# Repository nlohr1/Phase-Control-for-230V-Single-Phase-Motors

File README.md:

### Readme-Content:
- [Basic Schematic](#phase-control-for-230v-single-phase-motors-v2)
- [Module-Alignments](#alignment-v2-of-used-modules-on-a-5mm-acrylic-base-board)
- [Main-Schematic](#main-schematic--wiring-connections)
- [Safety-features](#safety-features)
- [Disclaimer](#readme-contents)
- [Principle-description](#principle-description)
- [The Wiring Board](#the-wiring-board)
- [Speedometer](#speedometer)
- [Schematic and Layout of the DIY-Speedometer](#diy-speedometer)
- [DIY-Boards + PCB-Layout](#diy-boards)

# Phase-Control-for-230V-Single-Phase-Motors
### Corrections and small modifications on new version Main_v2:  
- Another alignment purpose, which saves space.  
- The Emergency-Switch now is placed correctly within the "Off"-Switch wiring-line. Previoulsy it was wrongly placed within "On"-Switch line.  
- A second, passive 220k&Omega;2W-Resistor is placed after the Reversing-Switch between the two Motor-Supply-Lines (U1 and U2), instead on the wiring-board, to ensure save voltage-unload of the Motor-"Fire" EMI-Filter.

**⇒ &nbsp;New files in v2:**  
&#45; Main_v2 (base-folder for v2)  
&#45; Wiring-Board-Nano_v2 (sub-folder)  

This is a Control-Board for direction-switchable 230V *direct current* (DC)-motors, whose speed (rpm) can be controlled using a Potentiometer *or*  
using a PWM (Pulse Width Modulation) Signal in the low voltage range, generated here by a microController (Arduino Nano).

&nbsp; &nbsp;*Phase-Control schematic: **Priciple for 230V DC-Motors** with reversing-switch.*  

The picture above shows a basic diagram for the electronic control of a 230V **DC** motor, e.g. a hobby lathe, connected to a **single-phase** (230V) **AC**-current network.

Phase control circuits are often used for simple speed controls, here with an additional Bridge-Rectifier for 230V DC electric motors,
which are often used in medium power hobby machines (up to 10 amps ≙ approx. 2300 watts), such as lathes, milling benches, etc.

### Alignment-v2 of used modules on a 5mm acrylic base-board:
  
Since electronic controls of 230V *DC* motors in today's hobby machines (such as lathes, milling benches, etc.) often are built with
inexpensive components that are not really protected against surges or current peaks – some electronic-failures are inevitable.
So I decided to use a circuit that works a little more reliable, with electronic components and *modules* that are readily available
on the market *and* at the same time are better protected against voltage-glitches, overloads, incorrect operations and engine over-temperature.
All 230VDC (Direct Current!) brushed motors with up-to 2300 Watts can be controlled with this phase control board. It allows to control
the speed of the motor (0-100%) as well as the motor direction of rotation.

### Main Schematic / Wiring Connections:
⇒ *(the DIY-Wiring-Board with the Ardujino-nano here is yellow-framed)*

## Safety features
This circuit has some essential safety-functions:
- The main module "Kemo-M240" used here contains an integrated soft start, needed to start up strong motors (>800 - 2300 Watts),
   to avoid the tripping of standard 16A household fuses
- This main-module also contains an automatic overload or anti-lock shutdown with electronic reset
- If the used Motor contains a built-in NTC-thermistor (with 100kOhm), the µController can provide a protection against
   engine overheatings: if the motor-temperature exceeds 80°C, the µC goes into an endless loop, and reactivating PWM
   is only possible by switching off (main-power) or by pushing the reset-button of the µC.

!!!: Protection against direction of rotation switching ***while driving*** is **NOT** provided: if so an "EMF short circuit" occurs,
the "Kemo-M240" controller shots the power-control off in a fractions of a second and thus at least the mechanics of the machine is protected.
Electronics then can only be reactivated after a complete restart - either per µContoller-Reset or after a complete Main-Power Shutdown.

## Disclaimer:  
!!! It goes without saying that you reproduce this circuit at your own risk and responsibility !!!
Anyone who does not have sufficient knowledge of how to handle *dangerous* 230VAC currents or 325VDC(ss) voltages(!):
If you are not familiar with electrical or electronic components, you should either hire a specialist to do it for you
or stay away from it!
“Experiments” without special knowledge and appropriate protection(s) on high voltages can quickly end in death
following an electric shock! And sudden cardiac-arrest can occur even days after an electric shock! - if then
no immediate help is nearby...
In any case, a replica of this project is done expressly and explicitly *at your own risk*!

**Further notes:**
- Three-phase motor control is excluded due to the principle! This circuit only controls single phase Engines!
- The circuit also works with (simpler) *AC* single-phase asynchronous motors - omitting the bridge rectifier used here.
   However, a connected ***AC*** motor then is no longer direction-reversible.
- It is NOT suitable for capacitor motors! - "Capacitor starting motors" are often only used for simple purposes and
   built+used for on/off operation only (such as for smaller hobby drill press machines) - and are not speed-regulated.
   But it depends specifically on the type of engine, some capacitor motors can still be regulated (speed-limited).
   However, any weak to poor efficiency that so occurs should be taken into account (including heat losses).

Factual suggestions for improvements and changes are always welcome!

## Principle description:
The control works according to the 230VAC phase control principle (similar to a lamp dimmer), but in contrast to this
it can neutralize EMF (electromotive forces) of greater motors and is determined by special selection of used electronic components.

The Kemo-240 control-module is controlled via PWM (Pulse Width Modulation). This (low-voltage: 5VDC) PWM-signal is generated
with a “Arduino-Nano” micro-controller and (if present), this µC also evaluates an NTC-Sensor installed within the Motor, to check
a possible motor-overtemperature.
The Speedometer (RPM display on a LED display) does not run - as usually *independently* of the main phase-control, 
but sends back a "busy" signal to the µController, which therefore "knows" when the motor is running or not
(=when it is standing still), in order to ensure active discharge of the triac snubber and the EMI or EMC-filters charged
through supplied voltages + motor back EMF, to avoid uncontrolled jerky startings of the DC-motor after changing the direction of rotation.

The control consists of several modules chained(wired) one behind the other:

1. the 10AT fuse (F1) and the on/off switch with the self-holding latching contactor,
2. the (mandatory) safety switches plus other 230V safety microswitches on the specific machine,
3. the upstream EMC filter (= ElectroMagnetic Compatibility), here called EMI filter (serves to avoid incoming E.M. interferences),
4. the actual (triac) phase control, using *either* a potentiometer *or* a µController with PWM-output (Pulse-Width Modulation),
5. in parallel the 5V low-voltage circuit with the "Arduino-Nano" module, to generate the PWM for the phase control (2nd. version), 
   with additional, software-side monitoring of eventual motor-over-temperature,
6. the 15A/1500V bridge rectifier,
7. the reversing switch, also called “pole inverter” or direction of rotation switch,
8. a second EMI (carbon-brush-"fire"-) suppression filter + a second 10AT motor fuse (F2), and
9. at last the 325V DC (=direct current) motor.

230v-Wiring between modules and the outside-parts (rear 230V inlet-panel, front machine-control-panel, motor-connections) have to be connected safely
through PVC-isolated 1mm² wires (about AWG 17) and in-between through isolated threaded-connectors or clamping-connectors with 16A/230V.
I used lever clamps ("WAGO Hebelklemme 221-2411") for most of the "flying"-connections.  
For all 5Volt (=low-voltage) connections I used smaller wires (about 0.25-0.75mm² = AWG-23 upto AWG-20) with JST-Connectors (2-, 3- and 4-wired),
as connectors for the wiring-board. Of course also it's possible to use above mentionned WAGO-connectors for smaller wires.  
**Att: Reliability of connections** is VERY IMPORTANT, so dont choose cheap (=mostly bad) connectors, due to 99% of all electical problems
are resulting from loose contacts/connections!

## The Wiring Board:
The two DIY-parts in this chain that still needs to be soldered together + programmed are the “wiring board” and the DIY-Speedometer.  
The Wiring-board serves to wire/connect the Low-Voltage PWM-Signal to the main phase control module "Kemo-M240" and to other low-voltage connections
as the Panel-Signal-"On"-LED, the NTC-Sensor and the 10k&Omega;-Poti.  
This wiring board also contains the Arduino Nano µController as the heart of the circuit, some passive components (resistors + capacitors) and above mentionned
(JST-)Connectors plus a 4-wire JST-Connector for the Speedometer (rpm display) and the 230VAC Discharge Circuit (Power-Resistor), this to avoid uncontrolled,
jerk startings of the motor while switching it into reverse-direction.

*Circuit diagram of the low-voltage circuit "wiring board" with the Arduino Nano*  

This wiring board with the Arduino Nano is provided as schematic and as PCB-layout in Eagle format - which can easily be converted
into other formats. Included are also .pdf-files and layouts, prepared for the DIY "toner-direct-method" and for external PCB-Services.

## Speedometer:

## DIY-Speedometer:

**Schematic and Layout of the DIY-Speedometer**:  

The DIY-Speedometer consists of a 4-digit LED-display-module and a "Arduino Mini Pro"-module (inside the case) with 2 pieces of 10k resistors to GND.  
This tachometer can either be “manually wired”:
- by wire-connecting a 4-digit LED-Display module to a (Arduino-)Mini-Pro board + 2x 10k resistors to GND,
   or
- soldering SMD-parts on a DIY-Board with above provided layout. For this purpose I included Schematic + Layout, as well as BOM (Bill of Materials).

A speedometer to display the speed of the motor can also be purchased as a (ready-made) module - but this modules have no "running" monitor Signal and
so the discharge-unit (on the wiring-board) is no longer switching on/off (as needed for the 15k-Resistor R9).

## DIY-Boards:
Anyone who is familiar with DIY-etching of circuit boards can either use the 2-sided Toner Direct Method (see .pdf plans for 2-sided copy in 1:1 scale) or
give-it-out to an external PCB layout-service.  
In a further -separate- article I will describe a new and simpler method to make exact 2-sided DIY-PCB-layouts through laser-burning "resting"
ink-protect areas on the PCB-board (resting "black" areas: substracted isolated wiring-lines from the total surface).

All Documents are available as Eagle layouts, png-Image-Files and pdf-Files and also as Gerber+Excellon files (attached CAM .zip archives).  
So also both Arduino Sketches (for the Arduino-Nano "heart"-Module: "Firmware-Nano.ino" and the Sketch for the **DIY**-Speedometer-*Board* including a "naked"
ATmega328-µController + 4x7-LED-Display ***or*** for the wired version with an Ardino-Mini-Pro-*Module* + 4x7-LED-Display(-module).  
Both variants of the DIY-Speedometer are using the "Tachometer-using-Arduino.ino" sketch.  

Thereto I've enclosed also a 3D-printable case + frame-parts for the Tachometer, adapted to insert+glue the 4x7-LED-Display module.
-----

Github-Link: [https://github.com/nlohr1/Phase-Control-for-230V-Single-Phase-Motors](https://github.com/nlohr1/Phase-Control-for-230V-Single-Phase-Motors/blob/main/README.md)

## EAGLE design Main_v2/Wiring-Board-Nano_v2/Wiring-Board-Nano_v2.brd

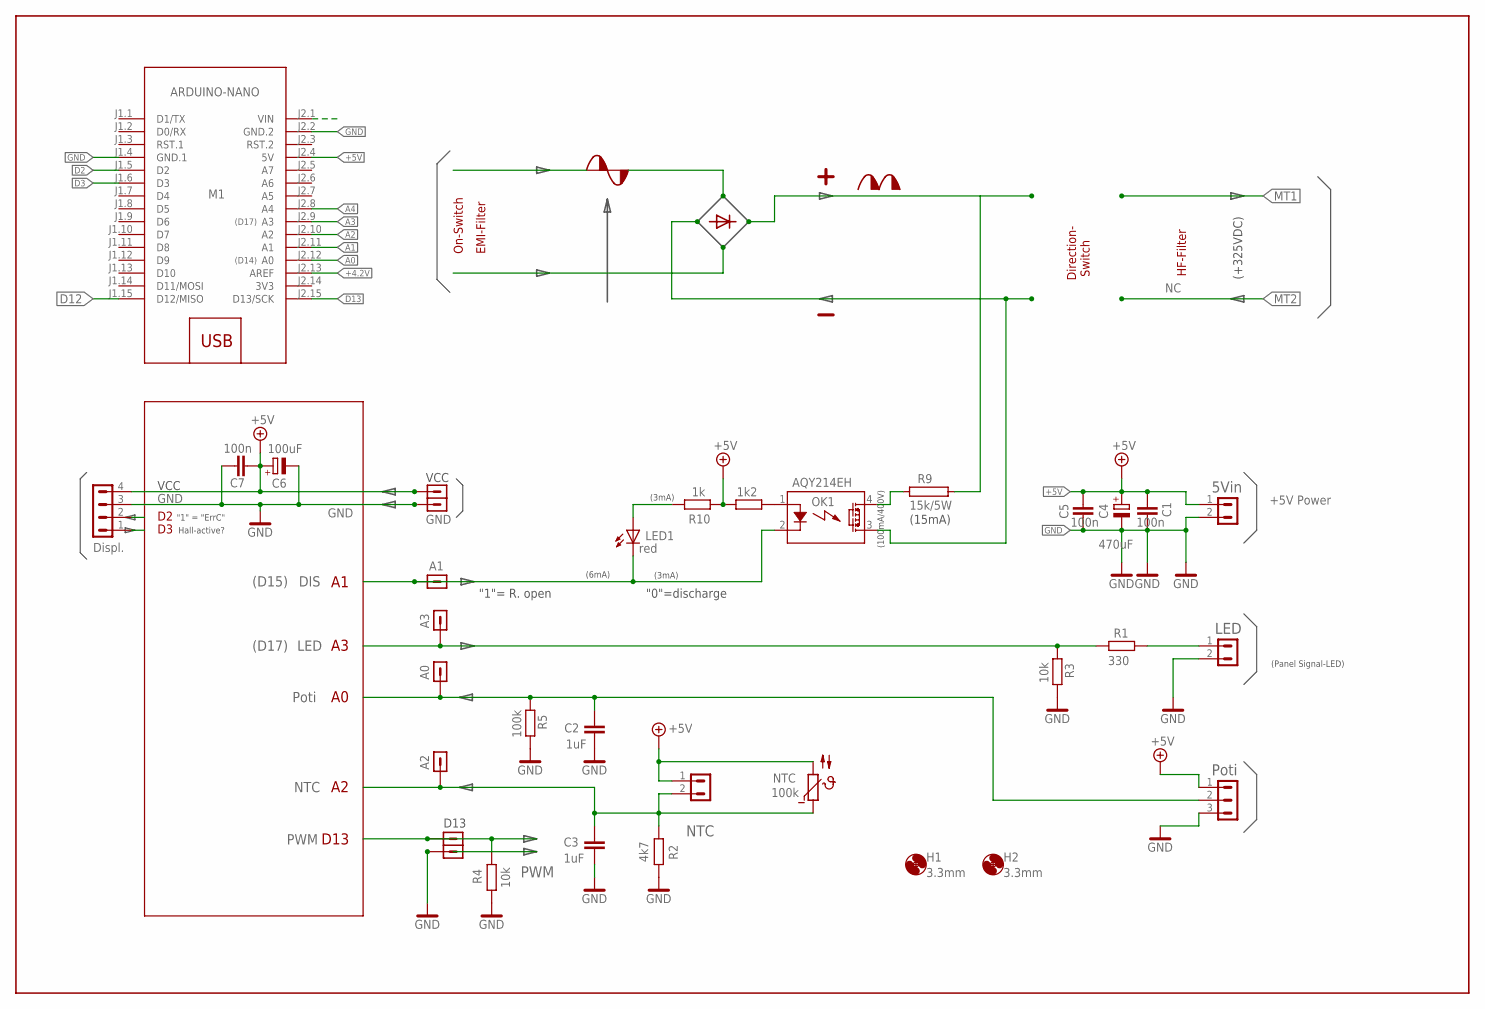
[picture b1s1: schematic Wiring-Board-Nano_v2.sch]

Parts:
C1, C5, C7: 100n; C0805
C2, C3: 1uF; C0805
C4: 470uF; E3,5-8
C6: 100uF; E2,5-7
H1, H2: 3.3mm; 3,3
LED1: red; CHIPLED_0805
M1: ARDUINO-NANO; ARDUINO-NANO-3.0
OK1: AQY214EH; GULLWING
R1: 330; R0805
R2: 4k7; R0805
R3, R4: 10k; R0805
R5: 100k; R0805
R9: 15k/5W; KH206-8
R10: 1k; R0805
R11: 1k2; R0805
SV1: 5Vin; MA02-1
SV2: LED; MA02-1
SV3: Poti; MA03-1
SV4: NTC; MA02-1
SV6: Displ.; MA04-1

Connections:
3V3: M1.J2.14 (3V3)
+4.2V: M1.J2.13 (AREF)
+5V: C1.1, C4.+, C5.1, C6.+, C7.1, M1.J2.4 (5V), R10.2, R11.1, SV1.1, SV3.1, SV4.1, SV6.4
A0: C2.1, M1.J2.12 (A0), R5.1, SV3.2
A1: LED1.C, M1.J2.11 (A1), OK1.2 (K)
A2: C3.1, M1.J2.10 (A2), R2.2, SV4.2
A3: M1.J2.9 (A3), R1.1, R3.1
A4: M1.J2.8 (A4)
D2: M1.J1.5 (D2), SV6.2
D3: M1.J1.6 (D3), SV6.1
D12: M1.J1.15 (D12/MISO)
D13: M1.J2.15 (D13/SCK), R4.1
GND: C1.2, C2.2, C3.2, C4.-, C5.2, C6.-, C7.2, M1.J1.4 (GND.1), M1.J2.2 (GND.2), R2.1, R3.2, R4.2, R5.2, SV1.2, SV2.2, SV3.3, SV6.3
MINUS: OK1.3 (DS2)
unnamed: OK1.1 (A), R11.2
unnamed: R1.2, SV2.1
unnamed: OK1.4 (DS1), R9.1
unnamed: LED1.A, R10.1
PLUS: R9.2

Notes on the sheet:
NTC
100k
D13
EMI-Filter
On-Switch
HF-Filter
(+325VDC)
Direction- Switch
+5V Power
(D17)
(D14)
(Panel Signal-LED)
Poti
LED
DIS
PWM
(D15)
GND
VCC
(15mA)
(100mA/400V)
(3mA)
Hall-active?
"1" = "ErrC"
"1"= R. open
(6mA)
"0"=discharge

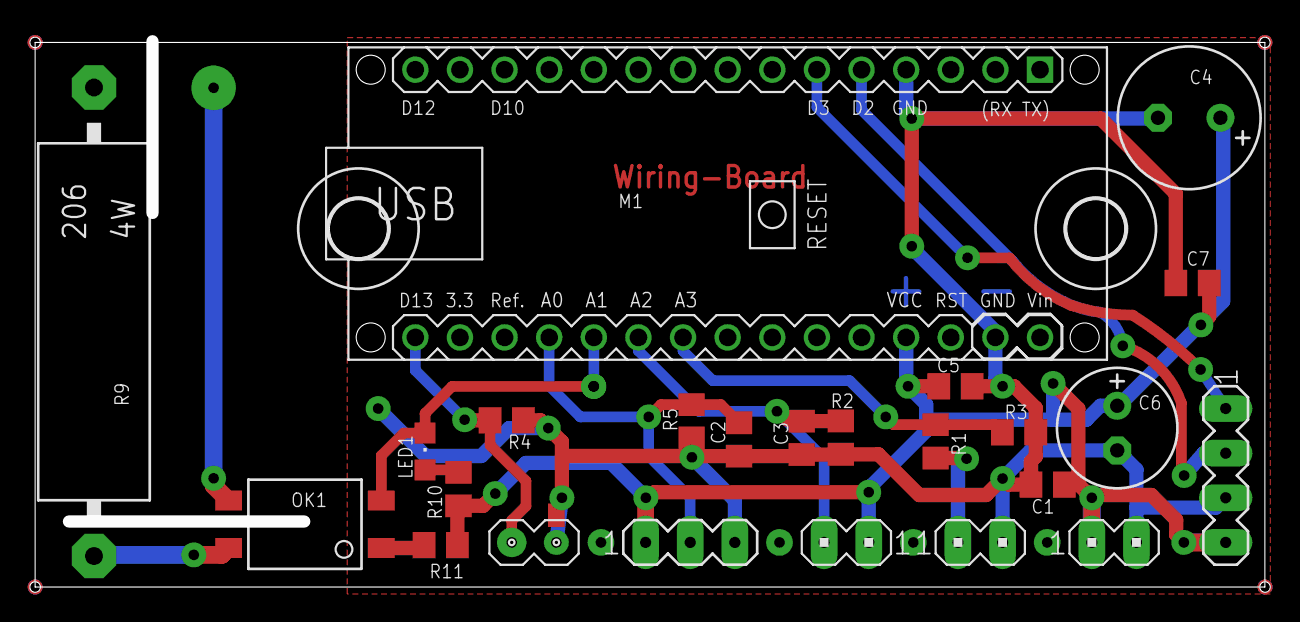
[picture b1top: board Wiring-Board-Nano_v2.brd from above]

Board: 2 copper layers, 69.3 x 30.7 mm, 25 parts (0 on the bottom side), 13 nets.

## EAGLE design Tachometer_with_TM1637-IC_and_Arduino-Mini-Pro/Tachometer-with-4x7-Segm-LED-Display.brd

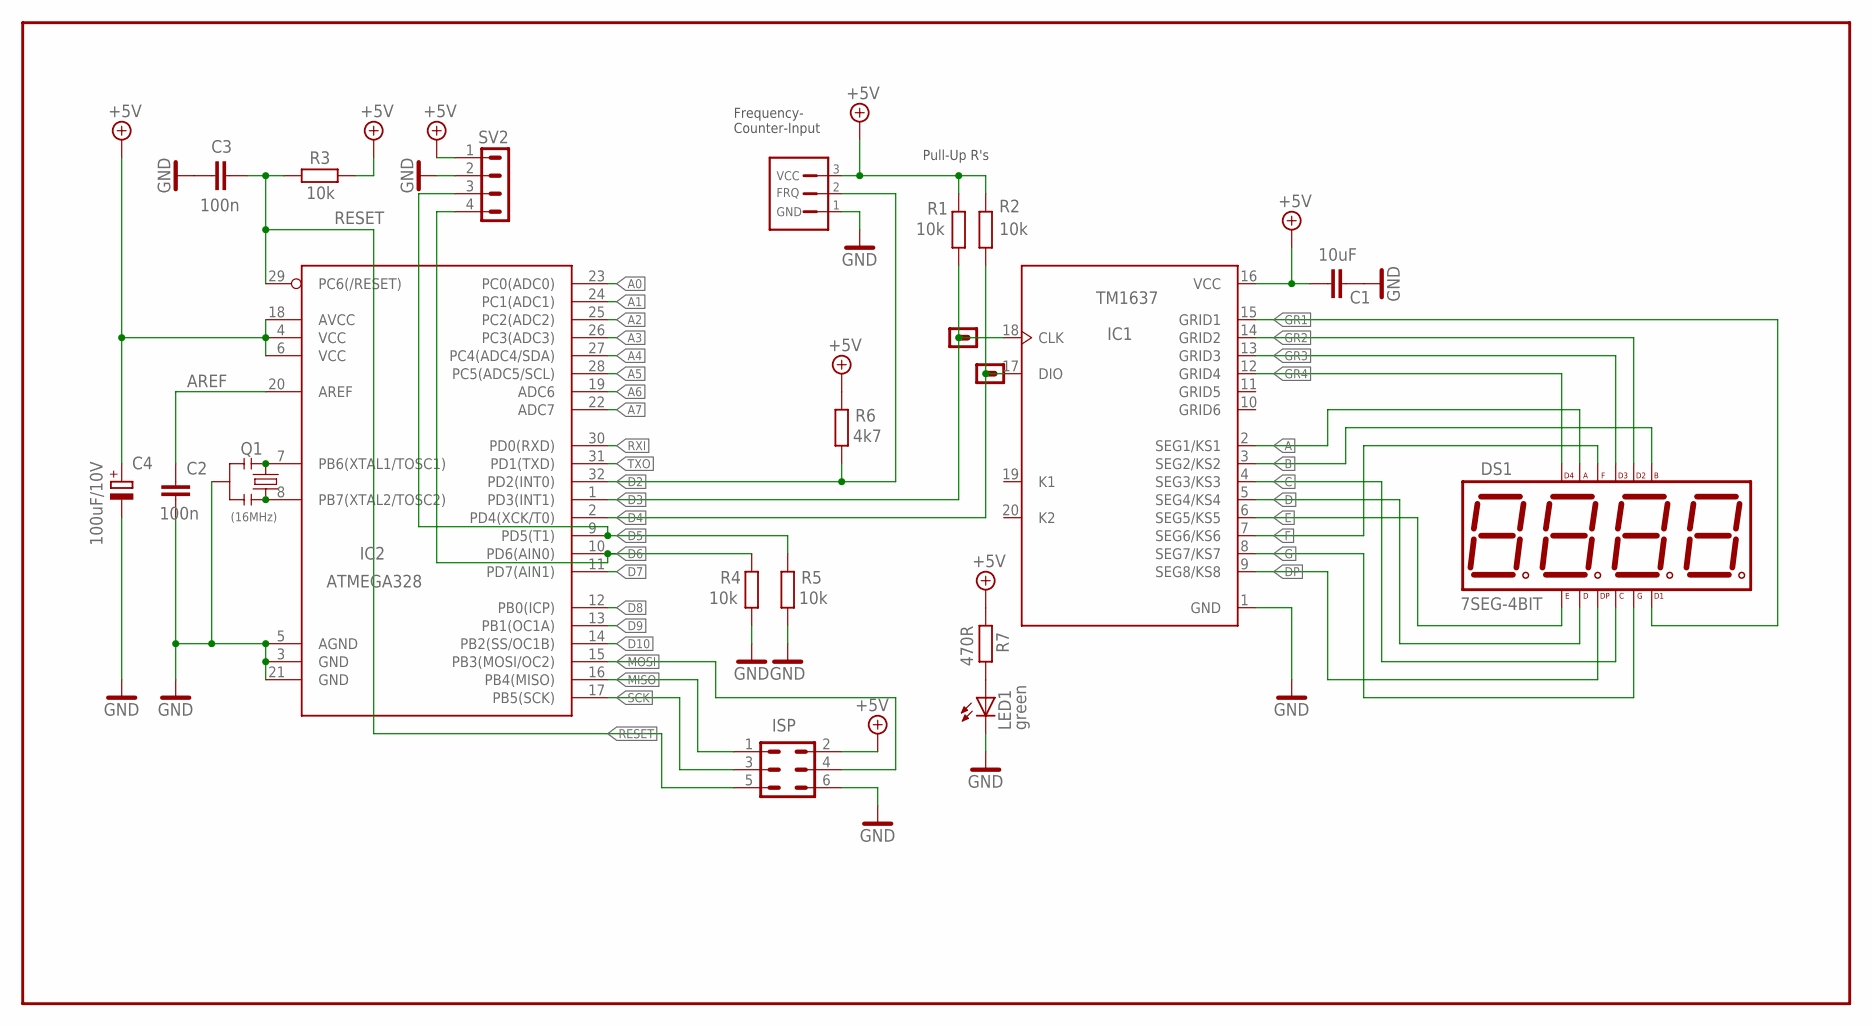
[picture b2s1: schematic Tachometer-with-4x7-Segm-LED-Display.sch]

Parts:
C1: 10uF; C0805
C2, C3: 100n; C0603
C4: 100uF/10V; E2,5-7
DS1: 7SEG-4BIT; 7SEG-14-4BIT
H: Hall-Ss.; 3JST-XH
IC1: TM1637; SOP-20
IC2: ATMEGA328; TQFP32-08
ISP: MA03-2
LED1: green; CHIPLED_0603
Q1: (16MHz); RESONATOR-SMD-1:1
R1, R2, R3, R4, R5: 10k; R0603
R6: 4k7; R0603
R7: 470R; R0603
SV2: MA04-10; MA04-1

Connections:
+5V: C1.1, C4.+, H.1, IC1.16 (VCC), IC2.4 (VCC), IC2.6 (VCC), IC2.18 (AVCC), ISP.2, R1.2, R2.2, R3.2, R6.2, R7.1, SV2.1
A: DS1.A, IC1.2 (SEG1/KS1)
A0: IC2.23 (PC0(ADC0))
A1: IC2.24 (PC1(ADC1))
A2: IC2.25 (PC2(ADC2))
A3: IC2.26 (PC3(ADC3))
A4: IC2.27 (PC4(ADC4/SDA))
A5: IC2.28 (PC5(ADC5/SCL))
A6: IC2.19 (ADC6)
A7: IC2.22 (ADC7)
AREF: C2.1, IC2.20 (AREF)
B: DS1.B, IC1.3 (SEG2/KS2)
C: DS1.C, IC1.4 (SEG3/KS3)
D: DS1.D, IC1.5 (SEG4/KS4)
D2: H.2, IC2.32 (PD2(INT0)), R6.1
D3: IC1.18 (CLK), IC2.1 (PD3(INT1)), R1.1
D4: IC1.17 (DIO), IC2.2 (PD4(XCK/T0)), R2.1
D5: IC2.9 (PD5(T1)), R5.2, SV2.3
D6: IC2.10 (PD6(AIN0)), R4.2, SV2.4
D7: IC2.11 (PD7(AIN1))
D8: IC2.12 (PB0(ICP))
D9: IC2.13 (PB1(OC1A))
D10: IC2.14 (PB2(SS/OC1B))
DP: DS1.DP, IC1.9 (SEG8/KS8)
E: DS1.E, IC1.6 (SEG5/KS5)
F: DS1.F, IC1.7 (SEG6/KS6)
G: DS1.G, IC1.8 (SEG7/KS7)
GND: C1.2, C2.2, C3.1, C4.-, H.3, IC1.1 (GND), IC2.3 (GND), IC2.5 (AGND), IC2.21 (GND), ISP.6, LED1.C, Q1.2, R4.1, R5.1, SV2.2
GR1: DS1.D1, IC1.15 (GRID1)
GR2: DS1.D2, IC1.14 (GRID2)
GR3: DS1.D3, IC1.13 (GRID3)
GR4: DS1.D4, IC1.12 (GRID4)
MISO: IC2.16 (PB4(MISO)), ISP.1
MOSI: IC2.15 (PB3(MOSI/OC2)), ISP.4
unnamed: LED1.A, R7.2
unnamed: IC2.8 (PB7(XTAL2/TOSC2)), Q1.3
unnamed: IC2.7 (PB6(XTAL1/TOSC1)), Q1.1
RESET: C3.2, IC2.29 (PC6(/RESET)), ISP.5, R3.1
RXI: IC2.30 (PD0(RXD))
SCK: IC2.17 (PB5(SCK)), ISP.3
TXO: IC2.31 (PD1(TXD))

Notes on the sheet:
FRQ
GND
VCC
Frequency- Counter-Input
Pull-Up R's

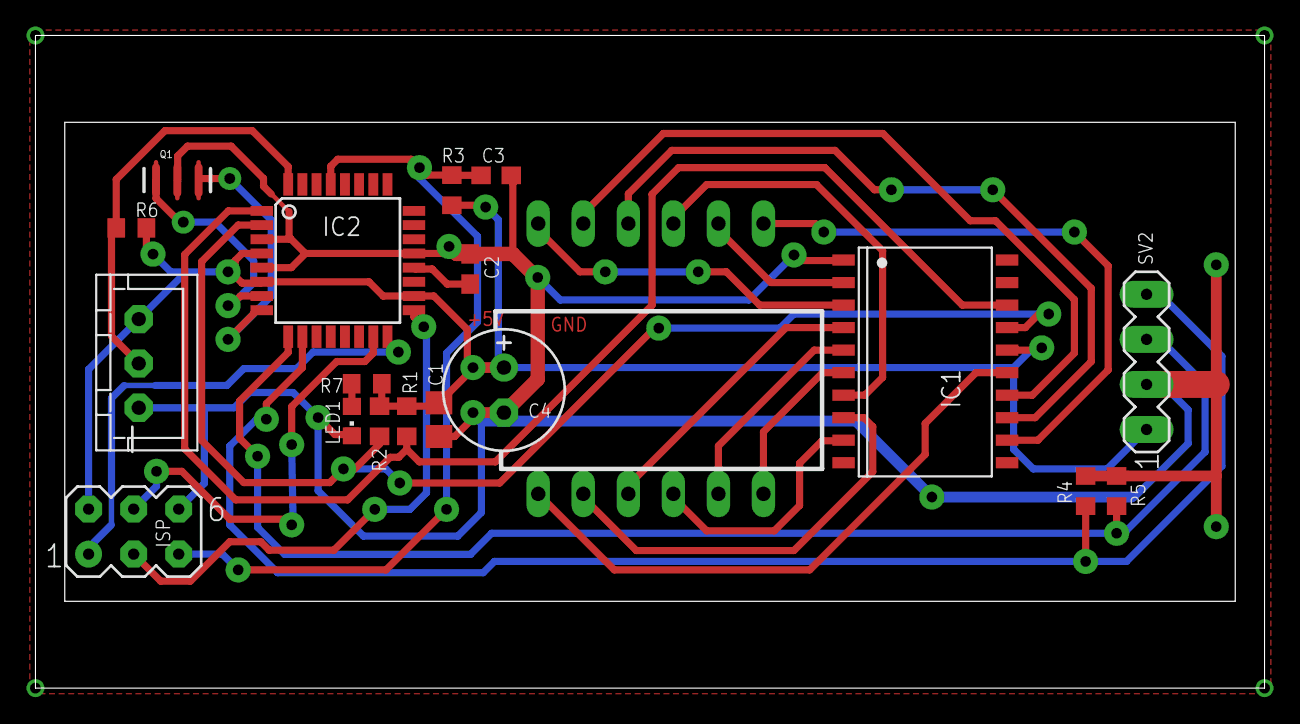
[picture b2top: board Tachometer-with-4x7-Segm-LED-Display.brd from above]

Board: 2 copper layers, 69.3 x 36.8 mm, 19 parts (1 on the bottom side), 27 nets.

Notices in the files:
parts and their libraries:
diy-modules: Released under the Creative Commons Attribution 4.0 International License: http://creativecommons.org/licenses/by/4.0
